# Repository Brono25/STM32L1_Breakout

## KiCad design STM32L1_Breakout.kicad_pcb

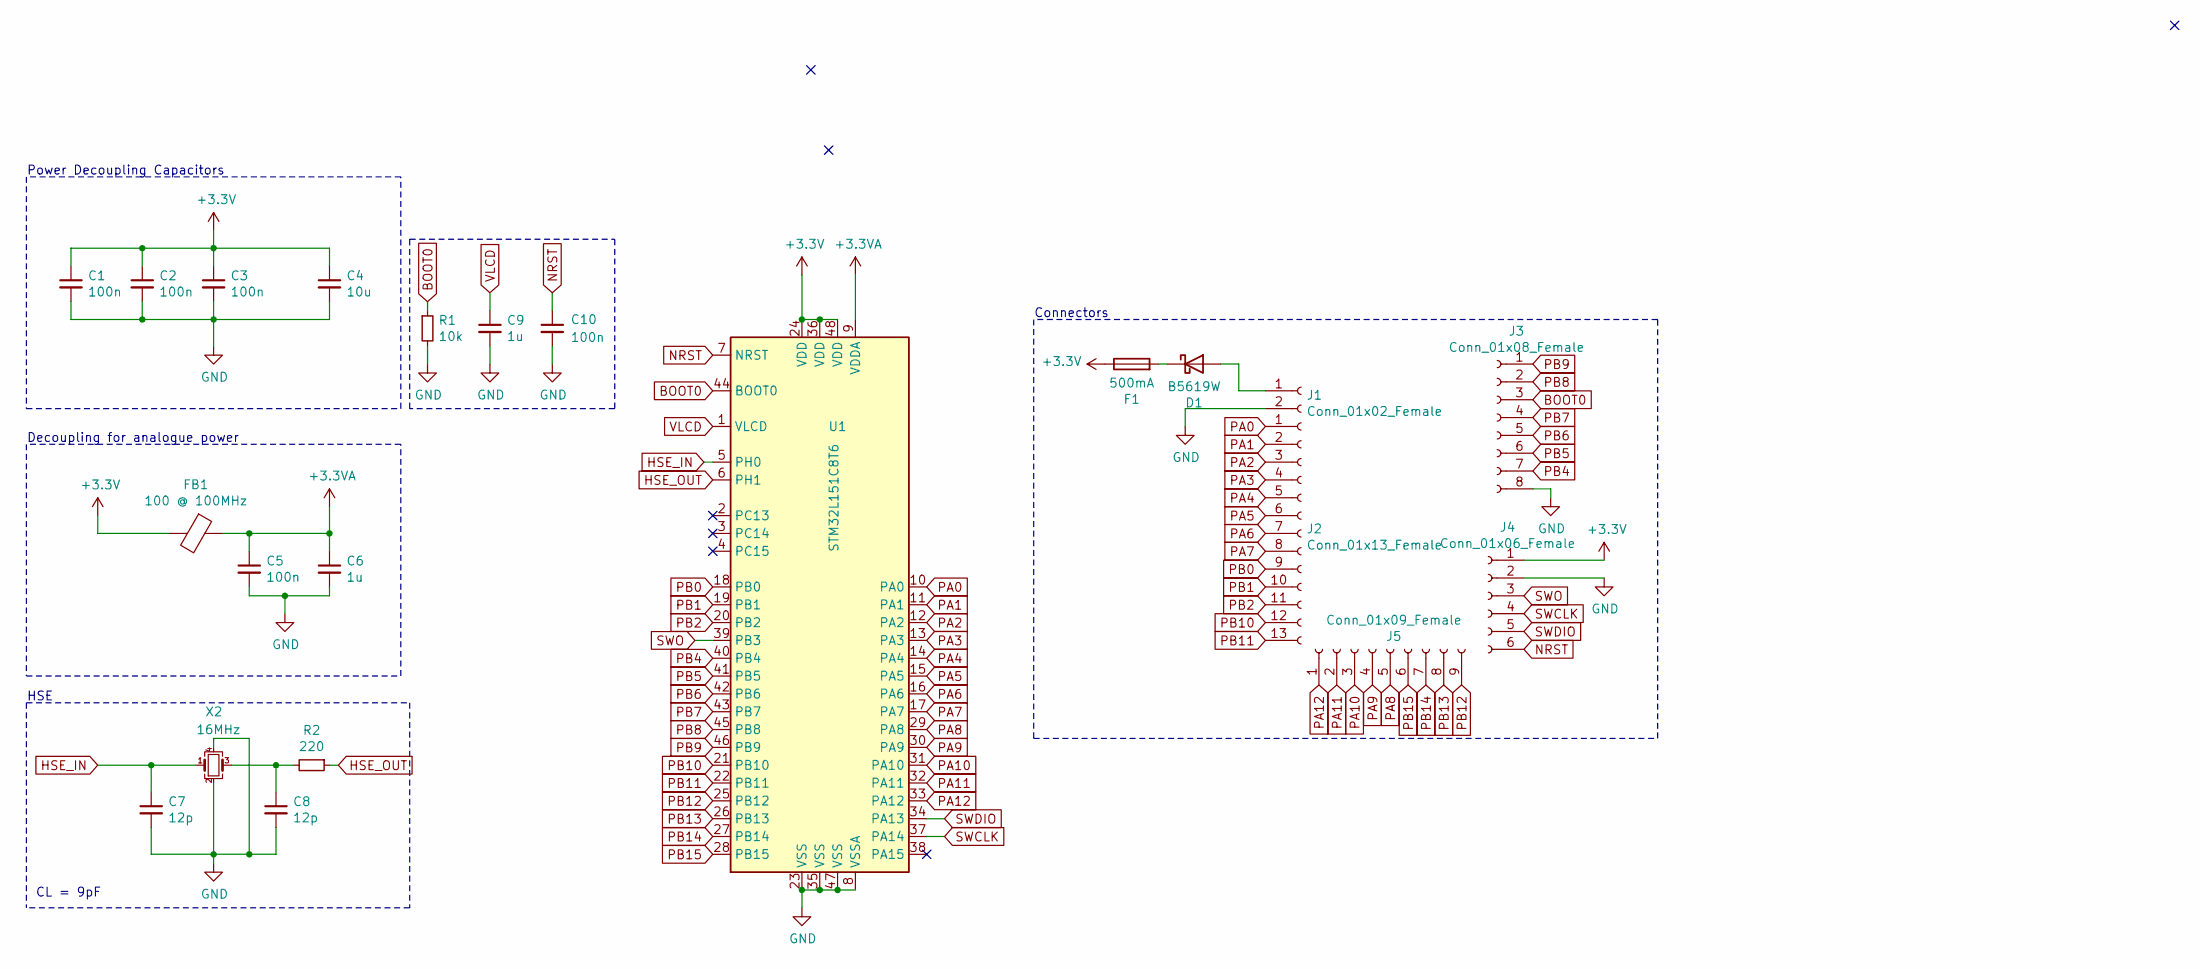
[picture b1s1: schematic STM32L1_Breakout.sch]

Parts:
C1, C2, C3, C5, C10: 100n; C_0603_1608Metric_Pad1.08x0.95mm_HandSolder
C4: 10u; C_0805_2012Metric_Pad1.18x1.45mm_HandSolder
C6, C9: 1u; C_0805_2012Metric_Pad1.18x1.45mm_HandSolder
C7, C8: 12p; C_0603_1608Metric_Pad1.08x0.95mm_HandSolder
D1: B5619W; D_SOD-123
F1: 500mA; Fuse_0603_1608Metric_Pad1.05x0.95mm_HandSolder
FB1: 100 @ 100MHz; L_0805_2012Metric_Pad1.15x1.40mm_HandSolder
J1: Conn_01x02_Female; PinSocket_1x02_P2.54mm_Vertical
J2: Conn_01x13_Female; PinSocket_1x13_P2.54mm_Vertical
J3: Conn_01x08_Female; PinSocket_1x08_P2.54mm_Vertical
J4: Conn_01x06_Female; PinSocket_1x06_P2.54mm_Vertical
J5: Conn_01x09_Female; PinSocket_1x09_P2.54mm_Vertical
R1: 10k; R_0603_1608Metric_Pad0.98x0.95mm_HandSolder
R2: 220; R_0603_1608Metric_Pad0.98x0.95mm_HandSolder
U1: STM32L151C8T6; LQFP-48_7x7mm_P0.5mm
X2: 16MHz; Crystal_SMD_3225-4Pin_3.2x2.5mm_HandSoldering

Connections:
+3.3VA: C5.1, C6.1, FB1.1, U1.9 (VDDA)
+3V3: C1.1, C2.1, C3.1, C4.1, F1.1, FB1.2, J4.1, U1.24 (VDD), U1.36 (VDD), U1.48 (VDD)
BOOT0: J3.3, R1.1, U1.44 (BOOT0)
GND: C1.2, C2.2, C3.2, C4.2, C5.2, C6.2, C7.2, C8.2, C9.2, C10.2, J1.2, J3.8, J4.2, R1.2, U1.8 (VSSA), U1.23 (VSS), U1.35 (VSS), U1.47 (VSS), X2.2, X2.4
HSE_IN: C7.1, U1.5 (PH0), X2.1
HSE_OUT: R2.1, U1.6 (PH1)
NRST: C10.1, J4.6, U1.7 (NRST)
unnamed: C8.1, R2.2, X2.3
unnamed: D1.1 (K), F1.2
unnamed: D1.2 (A), J1.1
PA0: J2.1, U1.10 (PA0)
PA1: J2.2, U1.11 (PA1)
PA2: J2.3, U1.12 (PA2)
PA3: J2.4, U1.13 (PA3)
PA4: J2.5, U1.14 (PA4)
PA5: J2.6, U1.15 (PA5)
PA6: J2.7, U1.16 (PA6)
PA7: J2.8, U1.17 (PA7)
PA8: J5.5, U1.29 (PA8)
PA9: J5.4, U1.30 (PA9)
PA10: J5.3, U1.31 (PA10)
PA11: J5.2, U1.32 (PA11)
PA12: J5.1, U1.33 (PA12)
PB0: J2.9, U1.18 (PB0)
PB1: J2.10, U1.19 (PB1)
PB2: J2.11, U1.20 (PB2)
PB4: J3.7, U1.40 (PB4)
PB5: J3.6, U1.41 (PB5)
PB6: J3.5, U1.42 (PB6)
PB7: J3.4, U1.43 (PB7)
PB8: J3.2, U1.45 (PB8)
PB9: J3.1, U1.46 (PB9)
PB10: J2.12, U1.21 (PB10)
PB11: J2.13, U1.22 (PB11)
PB12: J5.9, U1.25 (PB12)
PB13: J5.8, U1.26 (PB13)
PB14: J5.7, U1.27 (PB14)
PB15: J5.6, U1.28 (PB15)
SWCLK: J4.4, U1.37 (PA14)
SWDIO: J4.5, U1.34 (PA13)
SWO: J4.3, U1.39 (PB3)
VLCD: C9.1, U1.1 (VLCD)

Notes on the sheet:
Power Decoupling Capacitors
CL = 9pF
Decoupling for analogue power
Connectors
HSE

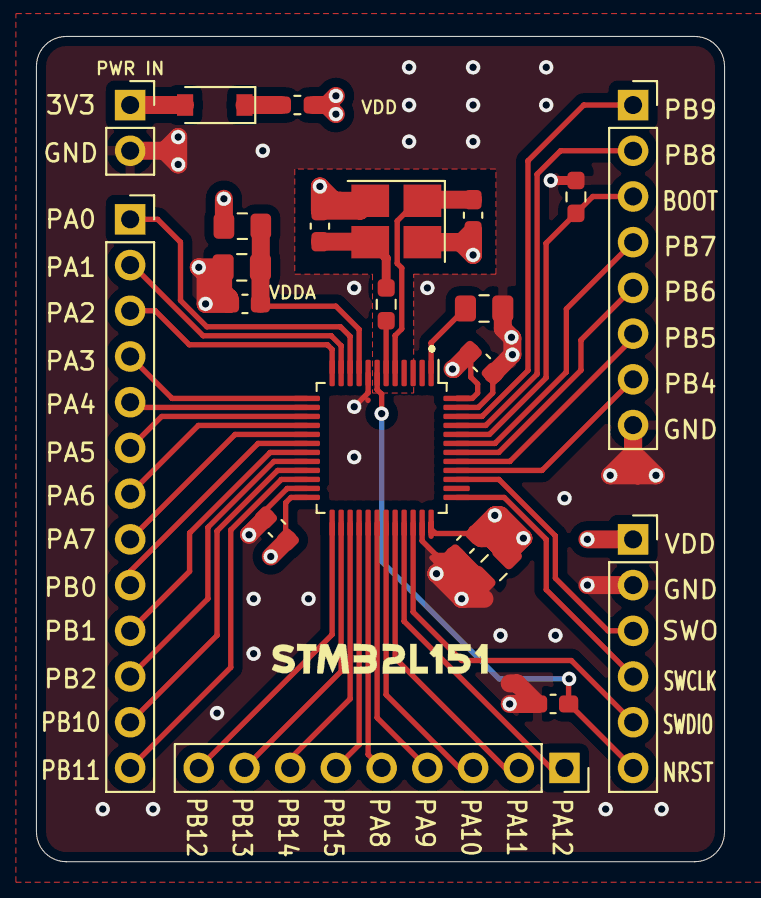
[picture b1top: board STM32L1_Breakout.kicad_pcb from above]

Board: 4 copper layers, 38.2 x 45.8 mm, 22 parts (0 on the bottom side), 42 nets.

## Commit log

2022-06-14 adding files
